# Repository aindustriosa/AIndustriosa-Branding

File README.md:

# AIndustriosa-Branding
Panel de logos de patrocinadores e colaboradores interactivo, construidos mediante ferramentas de fabricación dixital (Impresión 3D, corte laser, CNC…)

Durante este ano un dos proxectos propostos foi a elaboración dun novo panel de patrocinadores, intentando empregar todos os medios disponibles na Industriosa.

A idea era facer un panel interactivo de logos que se poidese integrar co Home Assistant do local, e usalo tamben de sinalítica.

A parte electrónica usamos tiras de led RGB de 5V coa idea que mediante sinxelas circuitos con un microcontrolador controlar cada panel.

Para empezar o deseño da base foi elaborada con InkScape.

Partindo los vectores modelamos nun programa de 3d mediante ferramentas de extrusión e operacións boleanas as bases e soportes los leds.

Con mesmo SVG sacamos os soportes dos leds de cada logo, deixando unha marxe para colocar as luces.

A maioria dos elementos foron impresos en 3d, dende as bases con PLA negro e as partes translucidas en PLA blanco con apenas 2 capas de recheo.

Para o deseño das pcbs, usamos o kicad, facendo unha sinxela placa cun Atiny412, dos saidas para duas tiras leds, toma de corrente e I2C, así como pin para programalos por UPDI

# Lista de materiais BOM

- Placas de Circuito de PCB **FR1** [Amazon](https://www.amazon.es/dp/B087M1GDCP?psc=1&smid=A839N7HCQOMKL&ref_=chk_typ_imgToDp)
- Fresa 0.4 End Mill -> 1/32 -> 0,4 MM -> TRACES [Aliexpress](https://es.aliexpress.com/item/32914096470.html?spm=a2g0o.order_list.0.0.19bb194dGODsyC&gatewayAdapt=glo2esp)
- Fresa 0.8 End Mill -> 1/64 -> 0,8 MM -> CUT [Aliexpress](https://es.aliexpress.com/item/32914096470.html?spm=a2g0o.order_list.0.0.19bb194dGODsyC&gatewayAdapt=glo2esp)

| Compoñente | Unidades | Código | Tenda | Footprint |
| ----- | ---- | ---- | ---- | ---- |
| ATtiny412 | 1 | ATTINY412-SSF-ND | [Digikey](https://www.digikey.es/en/products/detail/microchip-technology/ATTINY412-SSF/9947539) | SOIC-8_3.9x4.9mm_P1.27mm |
| Cap 10 uF | 1 | GRT31CC8YA106ME01L | [Digikey](https://www.digikey.es/en/products/detail/murata-electronics/GRT31CC8YA106ME01L/5416847) | C_1206 |
| Res 0 Ohms | 1 | RC1206FR-070RL | [Digikey](https://www.digikey.com/en/products/detail/yageo/RC1206FR-070RL/5698945) | R_1206 |
| Res 499 Ohms | 1 | RC1206FR-07499RL | [Digikey](https://www.digikey.es/en/products/detail/yageo/RC1206FR-07499RL/728944) | R_1206 |
| LED RED | 1 | 1516-1076-1-ND  | [Digikey](https://www.digikey.es/es/products/detail/qt-brightek-qtb/QBLP615-R/4814674) | LED_1206 |
| Connector 1x03_P2.54mm_Horizontal | 3 | S1143E-36-ND  | [Digikey](https://www.digikey.es/es/products/detail/sullins-connector-solutions/GBC36SGSN-M89/862355) | PinHeader_1x03_P2.54mm_Horizontal_SMD |
| Connector 2x10_P2.54mm_Vertical | 3 | 20021121-00010T1LF  | [Digikey](https://www.digikey.es/en/products/detail/amphenol-icc-fci/20021121-00010T1LF/4243614) | PinHeader_1x03_P2.54mm_Horizontal_SMD |

Unha vez tiñamos o deseño da PCB exportamos a SVG a capa frontal e a capa de corte, para mediante GIMP xerar os png para facer of gcode con <a href="https://modsproject.org" target="_blank">ModsProject</a>.

Unha vez xerados os gcode, nunha CNC 3018 da asociación, usando o <a href="https://winder.github.io/ugs_website/" target="_blank">UGS</a> fabricamos as placas.

Unha vez fabricado o primeiro prototipo, mediante Arduino IDE empezamos a programar o funcionamento los LEDs. 

Para programar o Atiny412 a libraría <a href="https://github.com/SpenceKonde/megaTinyCore" target="_blank">megaTinyCore</a>, que inclue control de <a href="https://github.com/SpenceKonde/megaTinyCore/blob/master/megaavr/extras/tinyNeoPixel.md" target="_blank">NeoPixel</a>

Debido o limite de memoria para usar más de 50 led, fixemos no código duas funcións onde despois de encender unha tira dun pin, liberamos a memoria, para encender os outros leds.

Con corte laser cortamos o panel en chopo de 3mm.

<b>Proxecto patrocinado por Xunta de Galicia e Amtega Axencia para a Modernización Tecnolóxica</b>

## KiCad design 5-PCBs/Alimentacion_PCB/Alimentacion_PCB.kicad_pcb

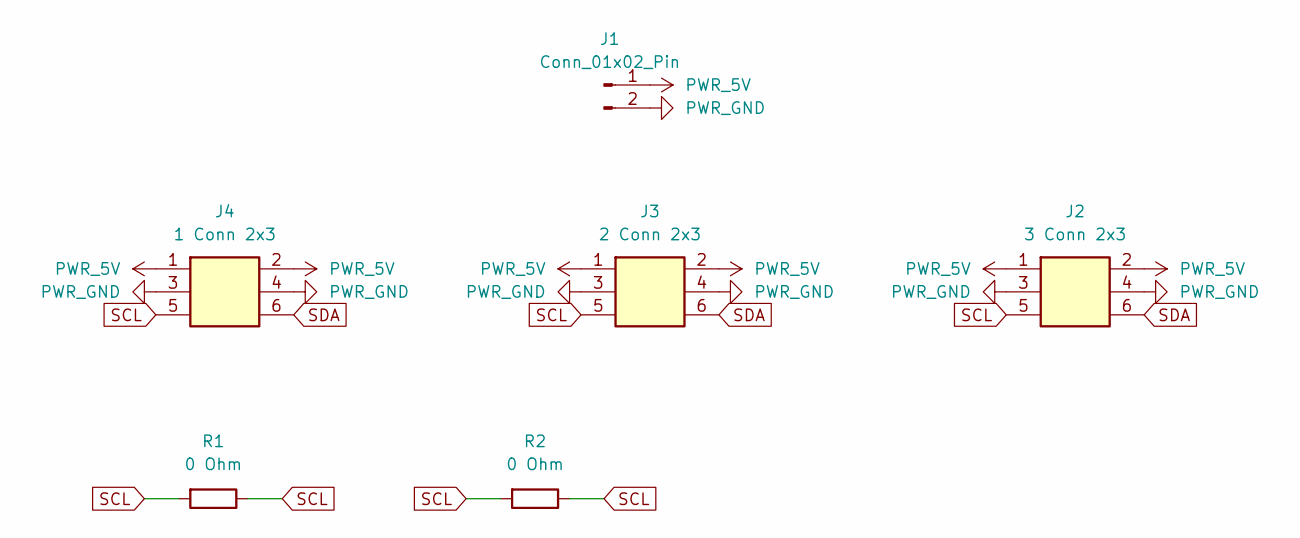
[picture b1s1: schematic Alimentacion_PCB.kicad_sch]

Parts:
J1: Conn_01x02_Pin; TE_2834006-2_1x02_P4.0mm_Horizontal
J2: 3 Conn 2x3; PinHeader_2x03_P2.54mm_Vertical_SMD
J3: 2 Conn 2x3; PinHeader_2x03_P2.54mm_Vertical_SMD
J4: 1 Conn 2x3; PinHeader_2x03_P2.54mm_Vertical_SMD
R1, R2: 0 Ohm; R_1206

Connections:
PWR_5V: J1.1, J2.1, J2.2, J3.1, J3.2, J4.1, J4.2
PWR_GND: J1.2, J2.3, J2.4, J3.3, J3.4, J4.3, J4.4
SCL: J2.5, J3.5, J4.5, R1.1, R1.2, R2.1, R2.2
SDA: J2.6, J3.6, J4.6

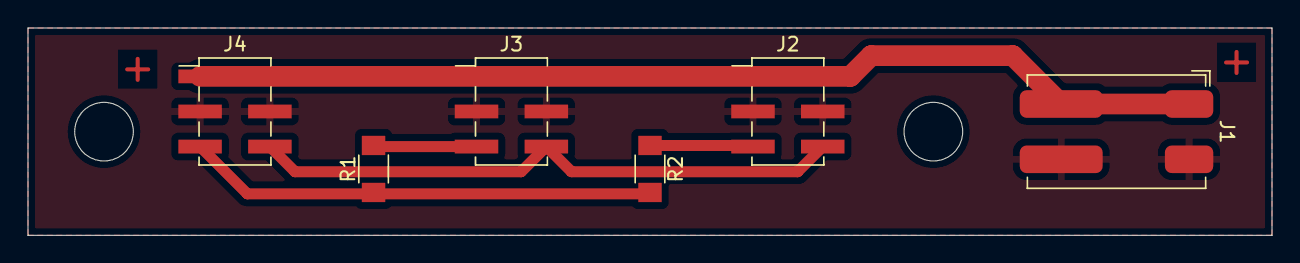
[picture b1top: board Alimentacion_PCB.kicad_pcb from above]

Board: 2 copper layers, 90.0 x 15.0 mm, 6 parts (0 on the bottom side), 4 nets.

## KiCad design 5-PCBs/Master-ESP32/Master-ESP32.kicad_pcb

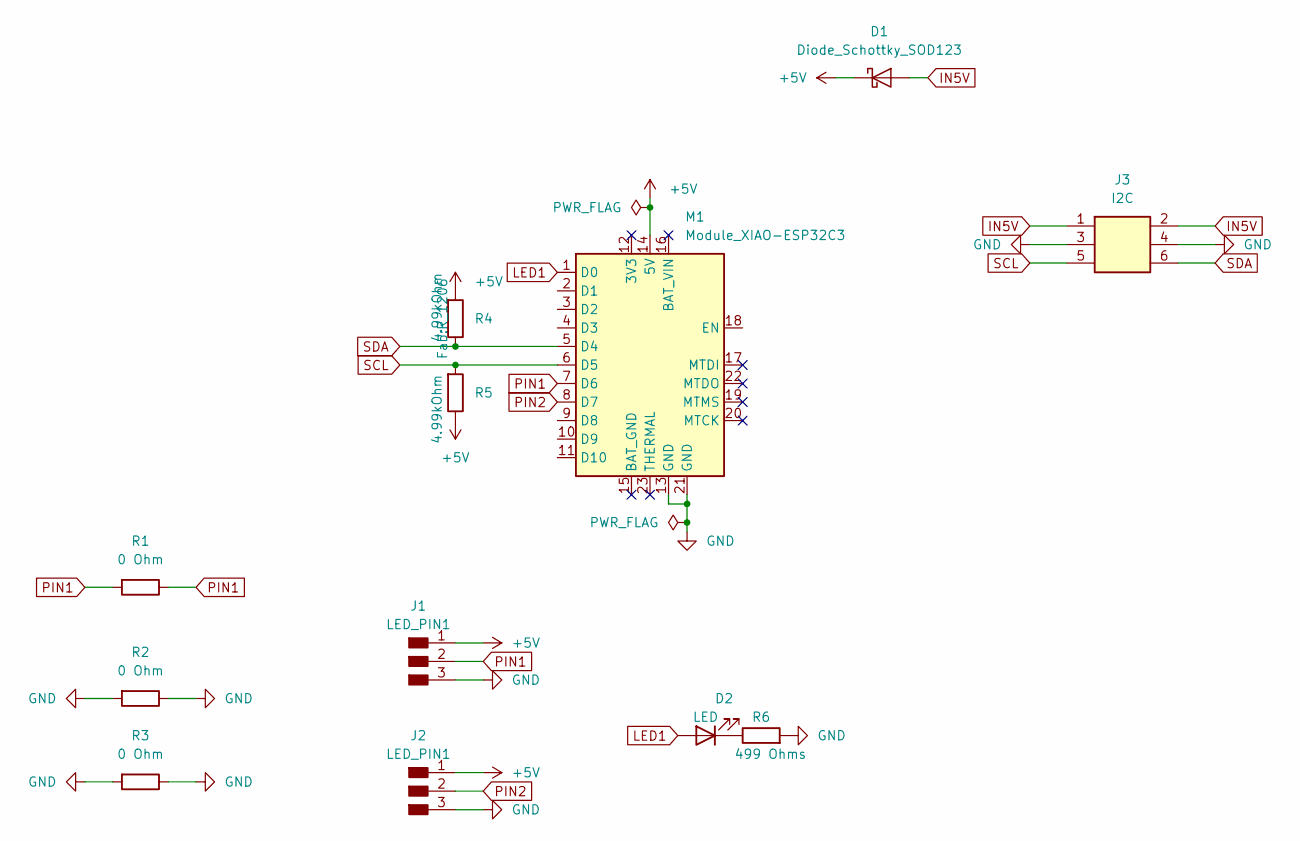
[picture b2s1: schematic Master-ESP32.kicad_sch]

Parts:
D1: Diode_Schottky_SOD123; SOD-123
D2: LED; LED_1206
J1, J2: LED_PIN1; PinHeader_1x03_P2.54mm_Horizontal_SMD
J3: I2C; PinHeader_2x03_P2.54mm_Vertical_SMD
M1: Module_XIAO-ESP32C3; SeeedStudio_XIAO_ESP32C3
R1, R2, R3: 0 Ohm; R_1206
R4, R5: 4.99kOhm; R_1206
R6: 499 Ohms; R_1206

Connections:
+5V: D1.1 (K), J1.1, J2.1, M1.14 (5V), R4.2, R5.1
GND: J1.3, J2.3, J3.3, J3.4, M1.13 (GND), M1.21 (GND), R2.1, R2.2, R3.1, R3.2, R6.2
IN5V: D1.2 (A), J3.1, J3.2
LED1: D2.2 (A), M1.1 (D0)
unnamed: D2.1 (K), R6.1
PIN1: J1.2, M1.7 (D6), R1.1, R1.2
PIN2: J2.2, M1.8 (D7)
SCL: J3.5, M1.6 (D5), R5.2
SDA: J3.6, M1.5 (D4), R4.1

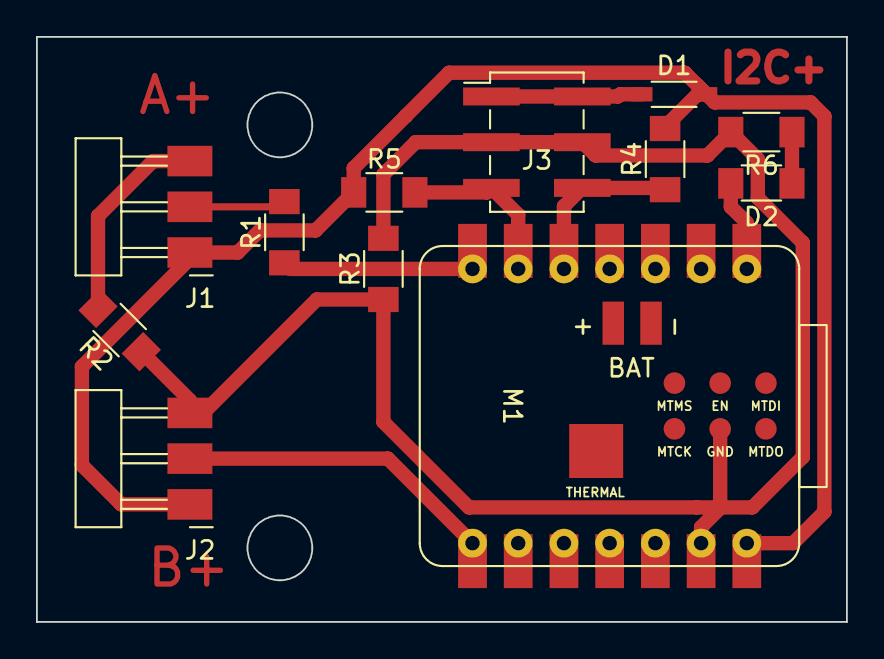
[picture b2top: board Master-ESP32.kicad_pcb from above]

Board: 2 copper layers, 45.0 x 32.5 mm, 12 parts (0 on the bottom side), 9 nets.

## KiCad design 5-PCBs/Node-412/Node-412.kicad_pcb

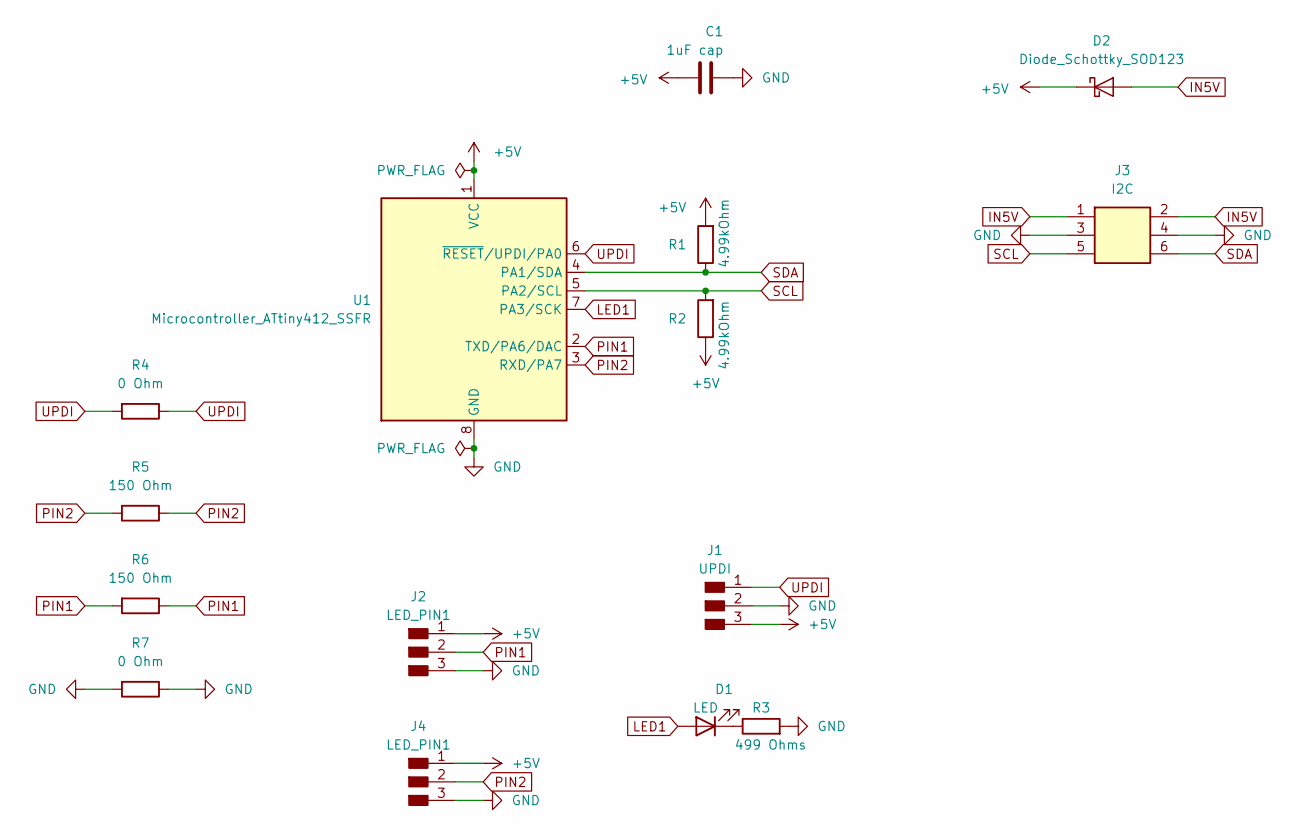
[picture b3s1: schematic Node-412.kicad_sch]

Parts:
C1: 1uF cap; C_1206
D1: LED; LED_1206
D2: Diode_Schottky_SOD123; SOD-123T
J1: UPDI; PinHeader_1x03_P2.54mm_Horizontal_SMD
J2, J4: LED_PIN1; PinHeader_1x03_P2.54mm_Horizontal_SMD
J3: I2C; PinHeader_2x03_P2.54mm_Vertical_SMD
R1, R2: 4.99kOhm; R_1206
R3: 499 Ohms; R_1206
R4, R7: 0 Ohm; R_1206
R5, R6: 150 Ohm; R_1206
U1: Microcontroller_ATtiny412_SSFR; SOIC-8_3.9x4.9mm_P1.27mm

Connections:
+5V: C1.1, D2.1 (K), J1.3, J2.1, J4.1, R1.2, R2.1, U1.1 (VCC)
GND: C1.2, J1.2, J2.3, J3.3, J3.4, J4.3, R3.2, R7.1, R7.2, U1.8 (GND)
IN5V: D2.2 (A), J3.1, J3.2
LED1: D1.2 (A), U1.7 (PA3/SCK)
unnamed: D1.1 (K), R3.1
PIN1: J2.2, R6.1, R6.2, U1.2 (TXD/PA6/DAC)
PIN2: J4.2, R5.1, R5.2, U1.3 (RXD/PA7)
SCL: J3.5, R2.2, U1.5 (PA2/SCL)
SDA: J3.6, R1.1, U1.4 (PA1/SDA)
UPDI: J1.1, R4.1, R4.2, U1.6 (~RESET/UPDI/PA0)

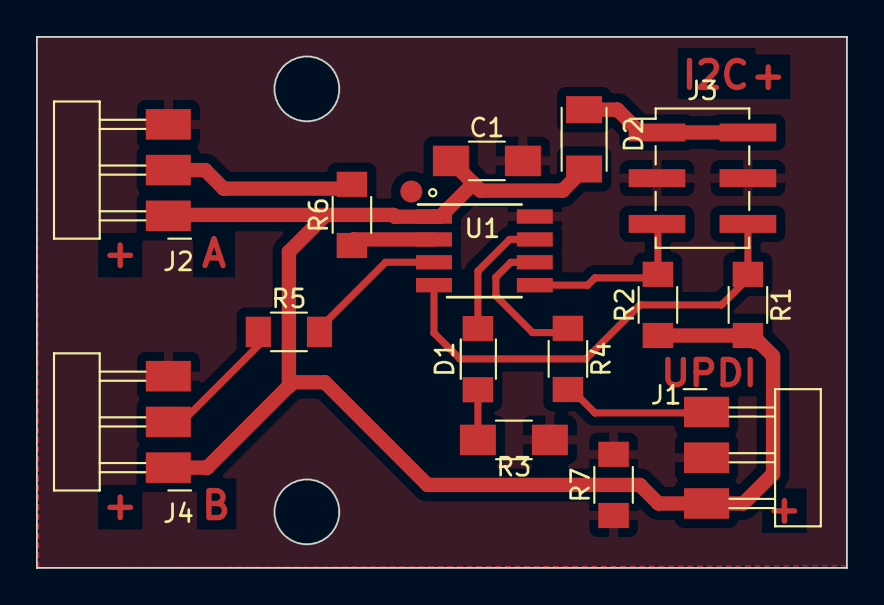
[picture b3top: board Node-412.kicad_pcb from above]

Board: 2 copper layers, 45.0 x 29.5 mm, 15 parts (0 on the bottom side), 10 nets.

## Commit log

2024-10-05 impresion 3D
2024-10-05 images
2024-10-08 upload
2024-10-30 alimentacion_PCB
